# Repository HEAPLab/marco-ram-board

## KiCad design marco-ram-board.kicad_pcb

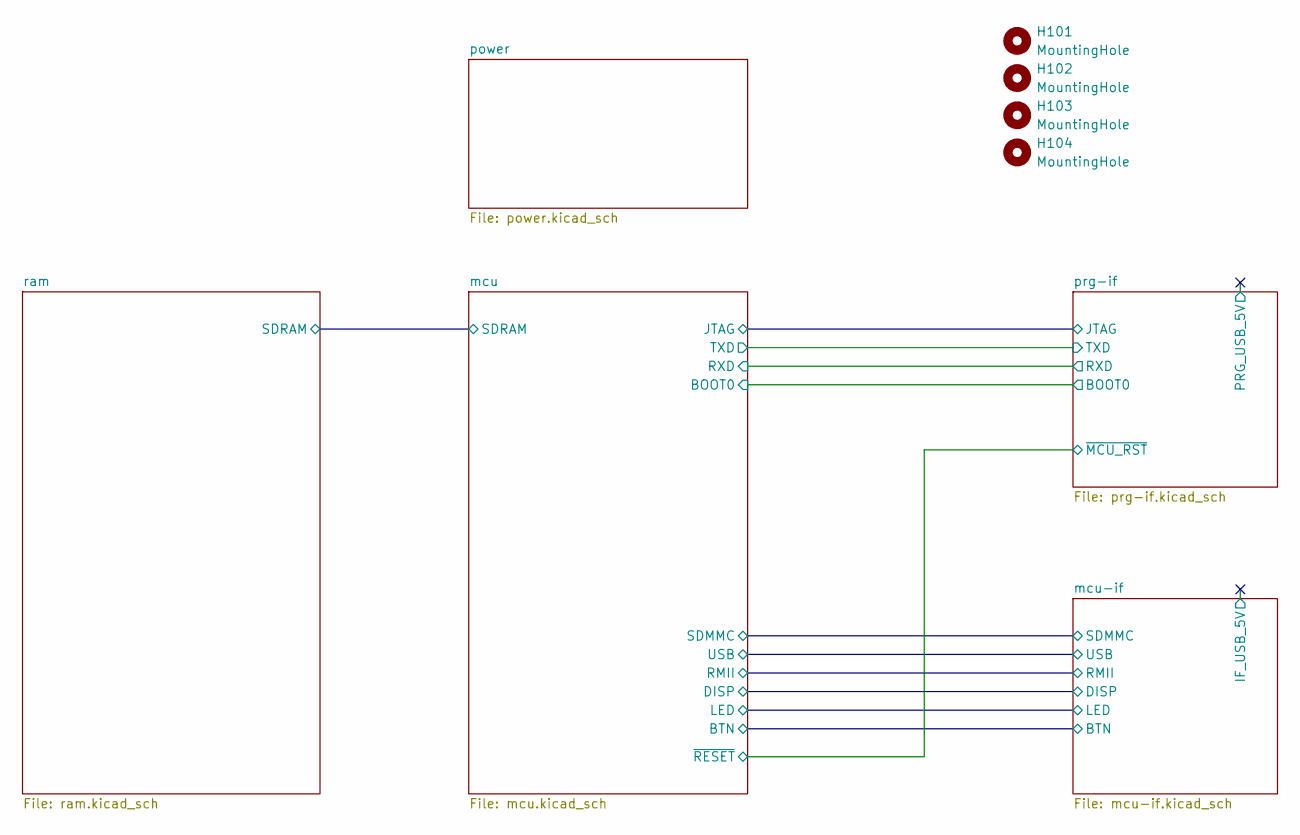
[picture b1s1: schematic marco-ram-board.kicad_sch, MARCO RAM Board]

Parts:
H101, H102, H103, H104: MountingHole; MountingHole_3.2mm_M3

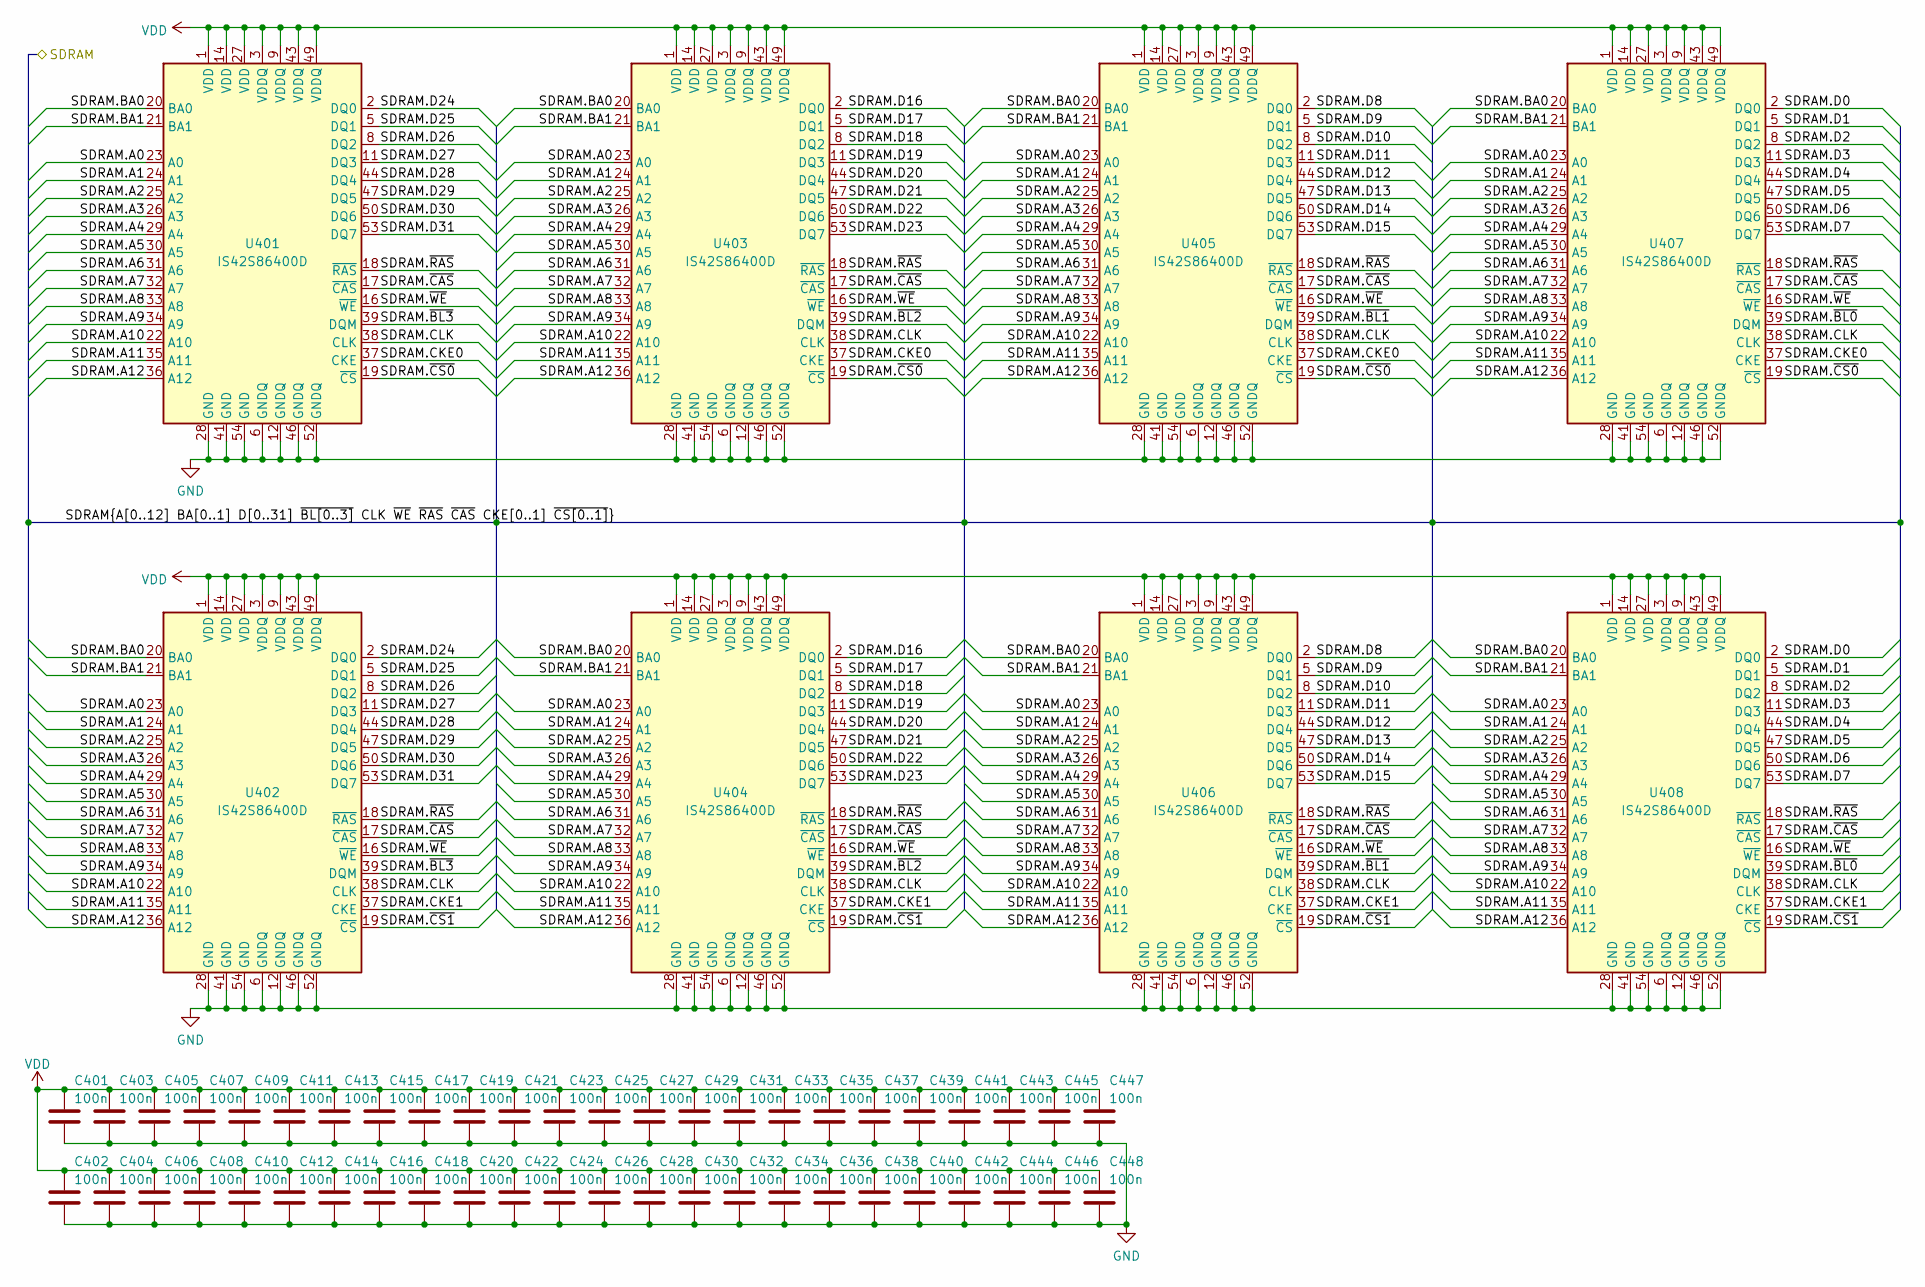
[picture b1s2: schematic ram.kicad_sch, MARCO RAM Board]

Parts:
C401, C402, C403, C404, C405, C406, C407, C408, C409, C410, C411, C412, C413, C414, C415, C416, C417, C418, C419, C420, C421, C422, C423, C424, C425, C426, C427, C428, C429, C430, C431, C432, C433, C434, C435, C436, C437, C438, C439, C440, C441, C442, C443, C444, C445, C446, C447, C448: 100n; C_0603_1608Metric_Pad1.08x0.95mm_HandSolder
U401, U402, U403, U404, U405, U406, U407, U408: IS42S86400D; TSOP-II-54_22.2x10.16mm_P0.8mm

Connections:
/mcu/SDRAM.A0: U401.23 (A0), U402.23 (A0), U403.23 (A0), U404.23 (A0), U405.23 (A0), U406.23 (A0), U407.23 (A0), U408.23 (A0); also elsewhere on the board
/mcu/SDRAM.A1: U401.24 (A1), U402.24 (A1), U403.24 (A1), U404.24 (A1), U405.24 (A1), U406.24 (A1), U407.24 (A1), U408.24 (A1); also elsewhere on the board
/mcu/SDRAM.A2: U401.25 (A2), U402.25 (A2), U403.25 (A2), U404.25 (A2), U405.25 (A2), U406.25 (A2), U407.25 (A2), U408.25 (A2); also elsewhere on the board
/mcu/SDRAM.A3: U401.26 (A3), U402.26 (A3), U403.26 (A3), U404.26 (A3), U405.26 (A3), U406.26 (A3), U407.26 (A3), U408.26 (A3); also elsewhere on the board
/mcu/SDRAM.A4: U401.29 (A4), U402.29 (A4), U403.29 (A4), U404.29 (A4), U405.29 (A4), U406.29 (A4), U407.29 (A4), U408.29 (A4); also elsewhere on the board
/mcu/SDRAM.A5: U401.30 (A5), U402.30 (A5), U403.30 (A5), U404.30 (A5), U405.30 (A5), U406.30 (A5), U407.30 (A5), U408.30 (A5); also elsewhere on the board
/mcu/SDRAM.A6: U401.31 (A6), U402.31 (A6), U403.31 (A6), U404.31 (A6), U405.31 (A6), U406.31 (A6), U407.31 (A6), U408.31 (A6); also elsewhere on the board
/mcu/SDRAM.A7: U401.32 (A7), U402.32 (A7), U403.32 (A7), U404.32 (A7), U405.32 (A7), U406.32 (A7), U407.32 (A7), U408.32 (A7); also elsewhere on the board
/mcu/SDRAM.A8: U401.33 (A8), U402.33 (A8), U403.33 (A8), U404.33 (A8), U405.33 (A8), U406.33 (A8), U407.33 (A8), U408.33 (A8); also elsewhere on the board
/mcu/SDRAM.A9: U401.34 (A9), U402.34 (A9), U403.34 (A9), U404.34 (A9), U405.34 (A9), U406.34 (A9), U407.34 (A9), U408.34 (A9); also elsewhere on the board
/mcu/SDRAM.A10: U401.22 (A10), U402.22 (A10), U403.22 (A10), U404.22 (A10), U405.22 (A10), U406.22 (A10), U407.22 (A10), U408.22 (A10); also elsewhere on the board
/mcu/SDRAM.A11: U401.35 (A11), U402.35 (A11), U403.35 (A11), U404.35 (A11), U405.35 (A11), U406.35 (A11), U407.35 (A11), U408.35 (A11); also elsewhere on the board
/mcu/SDRAM.A12: U401.36 (A12), U402.36 (A12), U403.36 (A12), U404.36 (A12), U405.36 (A12), U406.36 (A12), U407.36 (A12), U408.36 (A12); also elsewhere on the board
/mcu/SDRAM.BA0: U401.20 (BA0), U402.20 (BA0), U403.20 (BA0), U404.20 (BA0), U405.20 (BA0), U406.20 (BA0), U407.20 (BA0), U408.20 (BA0); also elsewhere on the board
/mcu/SDRAM.BA1: U401.21 (BA1), U402.21 (BA1), U403.21 (BA1), U404.21 (BA1), U405.21 (BA1), U406.21 (BA1), U407.21 (BA1), U408.21 (BA1); also elsewhere on the board
/mcu/SDRAM.CKE0: U401.37 (CKE), U403.37 (CKE), U405.37 (CKE), U407.37 (CKE); also elsewhere on the board
/mcu/SDRAM.CKE1: U402.37 (CKE), U404.37 (CKE), U406.37 (CKE), U408.37 (CKE); also elsewhere on the board
/mcu/SDRAM.CLK: U401.38 (CLK), U402.38 (CLK), U403.38 (CLK), U404.38 (CLK), U405.38 (CLK), U406.38 (CLK), U407.38 (CLK), U408.38 (CLK); also elsewhere on the board
/mcu/SDRAM.D0: U407.2 (DQ0), U408.2 (DQ0); also elsewhere on the board
/mcu/SDRAM.D1: U407.5 (DQ1), U408.5 (DQ1); also elsewhere on the board
/mcu/SDRAM.D2: U407.8 (DQ2), U408.8 (DQ2); also elsewhere on the board
/mcu/SDRAM.D3: U407.11 (DQ3), U408.11 (DQ3); also elsewhere on the board
/mcu/SDRAM.D4: U407.44 (DQ4), U408.44 (DQ4); also elsewhere on the board
/mcu/SDRAM.D5: U407.47 (DQ5), U408.47 (DQ5); also elsewhere on the board
/mcu/SDRAM.D6: U407.50 (DQ6), U408.50 (DQ6); also elsewhere on the board
/mcu/SDRAM.D7: U407.53 (DQ7), U408.53 (DQ7); also elsewhere on the board
/mcu/SDRAM.D8: U405.2 (DQ0), U406.2 (DQ0); also elsewhere on the board
/mcu/SDRAM.D9: U405.5 (DQ1), U406.5 (DQ1); also elsewhere on the board
/mcu/SDRAM.D10: U405.8 (DQ2), U406.8 (DQ2); also elsewhere on the board
/mcu/SDRAM.D11: U405.11 (DQ3), U406.11 (DQ3); also elsewhere on the board
/mcu/SDRAM.D12: U405.44 (DQ4), U406.44 (DQ4); also elsewhere on the board
/mcu/SDRAM.D13: U405.47 (DQ5), U406.47 (DQ5); also elsewhere on the board
/mcu/SDRAM.D14: U405.50 (DQ6), U406.50 (DQ6); also elsewhere on the board
/mcu/SDRAM.D15: U405.53 (DQ7), U406.53 (DQ7); also elsewhere on the board
/mcu/SDRAM.D16: U403.2 (DQ0), U404.2 (DQ0); also elsewhere on the board
/mcu/SDRAM.D17: U403.5 (DQ1), U404.5 (DQ1); also elsewhere on the board
/mcu/SDRAM.D18: U403.8 (DQ2), U404.8 (DQ2); also elsewhere on the board
/mcu/SDRAM.D19: U403.11 (DQ3), U404.11 (DQ3); also elsewhere on the board
/mcu/SDRAM.D20: U403.44 (DQ4), U404.44 (DQ4); also elsewhere on the board
/mcu/SDRAM.D21: U403.47 (DQ5), U404.47 (DQ5); also elsewhere on the board
/mcu/SDRAM.D22: U403.50 (DQ6), U404.50 (DQ6); also elsewhere on the board
/mcu/SDRAM.D23: U403.53 (DQ7), U404.53 (DQ7); also elsewhere on the board
/mcu/SDRAM.D24: U401.2 (DQ0), U402.2 (DQ0); also elsewhere on the board
/mcu/SDRAM.D25: U401.5 (DQ1), U402.5 (DQ1); also elsewhere on the board
/mcu/SDRAM.D26: U401.8 (DQ2), U402.8 (DQ2); also elsewhere on the board
/mcu/SDRAM.D27: U401.11 (DQ3), U402.11 (DQ3); also elsewhere on the board
/mcu/SDRAM.D28: U401.44 (DQ4), U402.44 (DQ4); also elsewhere on the board
/mcu/SDRAM.D29: U401.47 (DQ5), U402.47 (DQ5); also elsewhere on the board
/mcu/SDRAM.D30: U401.50 (DQ6), U402.50 (DQ6); also elsewhere on the board
/mcu/SDRAM.D31: U401.53 (DQ7), U402.53 (DQ7); also elsewhere on the board
/mcu/SDRAM.~BL0: U407.39 (DQM), U408.39 (DQM); also elsewhere on the board
/mcu/SDRAM.~BL1: U405.39 (DQM), U406.39 (DQM); also elsewhere on the board
/mcu/SDRAM.~BL2: U403.39 (DQM), U404.39 (DQM); also elsewhere on the board
/mcu/SDRAM.~BL3: U401.39 (DQM), U402.39 (DQM); also elsewhere on the board
/mcu/SDRAM.~CAS: U401.17 (~CAS), U402.17 (~CAS), U403.17 (~CAS), U404.17 (~CAS), U405.17 (~CAS), U406.17 (~CAS), U407.17 (~CAS), U408.17 (~CAS); also elsewhere on the board
/mcu/SDRAM.~CS0: U401.19 (~CS), U403.19 (~CS), U405.19 (~CS), U407.19 (~CS); also elsewhere on the board
/mcu/SDRAM.~CS1: U402.19 (~CS), U404.19 (~CS), U406.19 (~CS), U408.19 (~CS); also elsewhere on the board
/mcu/SDRAM.~RAS: U401.18 (~RAS), U402.18 (~RAS), U403.18 (~RAS), U404.18 (~RAS), U405.18 (~RAS), U406.18 (~RAS), U407.18 (~RAS), U408.18 (~RAS); also elsewhere on the board
/mcu/SDRAM.~WE: U401.16 (~WE), U402.16 (~WE), U403.16 (~WE), U404.16 (~WE), U405.16 (~WE), U406.16 (~WE), U407.16 (~WE), U408.16 (~WE); also elsewhere on the board
GND: C401.2, C402.2, C403.2, C404.2, C405.2, C406.2, C407.2, C408.2, C409.2, C410.2, C411.2, C412.2, C413.2, C414.2, C415.2, C416.2, C417.2, C418.2, C419.2, C420.2, C421.2, C422.2, C423.2, C424.2, C425.2, C426.2, C427.2, C428.2, C429.2, C430.2, C431.2, C432.2, C433.2, C434.2, C435.2, C436.2, C437.2, C438.2, C439.2, C440.2, C441.2, C442.2, C443.2, C444.2, C445.2, C446.2, C447.2, C448.2, U401.6 (GNDQ), U401.12 (GNDQ), U401.28 (GND), U401.41 (GND), U401.46 (GNDQ), U401.52 (GNDQ), U401.54 (GND), U402.6 (GNDQ), U402.12 (GNDQ), U402.28 (GND), U402.41 (GND), U402.46 (GNDQ), U402.52 (GNDQ), U402.54 (GND), U403.6 (GNDQ), U403.12 (GNDQ), U403.28 (GND), U403.41 (GND), U403.46 (GNDQ), U403.52 (GNDQ), U403.54 (GND), U404.6 (GNDQ), U404.12 (GNDQ), U404.28 (GND), U404.41 (GND), U404.46 (GNDQ), U404.52 (GNDQ), U404.54 (GND), U405.6 (GNDQ), U405.12 (GNDQ), U405.28 (GND), U405.41 (GND), U405.46 (GNDQ), U405.52 (GNDQ), U405.54 (GND), U406.6 (GNDQ), U406.12 (GNDQ), U406.28 (GND), U406.41 (GND), U406.46 (GNDQ), U406.52 (GNDQ), U406.54 (GND), U407.6 (GNDQ), U407.12 (GNDQ), U407.28 (GND), U407.41 (GND), U407.46 (GNDQ), U407.52 (GNDQ), U407.54 (GND), U408.6 (GNDQ), U408.12 (GNDQ), U408.28 (GND), U408.41 (GND), U408.46 (GNDQ), U408.52 (GNDQ), U408.54 (GND); also elsewhere on the board
VDD: C401.1, C402.1, C403.1, C404.1, C405.1, C406.1, C407.1, C408.1, C409.1, C410.1, C411.1, C412.1, C413.1, C414.1, C415.1, C416.1, C417.1, C418.1, C419.1, C420.1, C421.1, C422.1, C423.1, C424.1, C425.1, C426.1, C427.1, C428.1, C429.1, C430.1, C431.1, C432.1, C433.1, C434.1, C435.1, C436.1, C437.1, C438.1, C439.1, C440.1, C441.1, C442.1, C443.1, C444.1, C445.1, C446.1, C447.1, C448.1, U401.1 (VDD), U401.3 (VDDQ), U401.9 (VDDQ), U401.14 (VDD), U401.27 (VDD), U401.43 (VDDQ), U401.49 (VDDQ), U402.1 (VDD), U402.3 (VDDQ), U402.9 (VDDQ), U402.14 (VDD), U402.27 (VDD), U402.43 (VDDQ), U402.49 (VDDQ), U403.1 (VDD), U403.3 (VDDQ), U403.9 (VDDQ), U403.14 (VDD), U403.27 (VDD), U403.43 (VDDQ), U403.49 (VDDQ), U404.1 (VDD), U404.3 (VDDQ), U404.9 (VDDQ), U404.14 (VDD), U404.27 (VDD), U404.43 (VDDQ), U404.49 (VDDQ), U405.1 (VDD), U405.3 (VDDQ), U405.9 (VDDQ), U405.14 (VDD), U405.27 (VDD), U405.43 (VDDQ), U405.49 (VDDQ), U406.1 (VDD), U406.3 (VDDQ), U406.9 (VDDQ), U406.14 (VDD), U406.27 (VDD), U406.43 (VDDQ), U406.49 (VDDQ), U407.1 (VDD), U407.3 (VDDQ), U407.9 (VDDQ), U407.14 (VDD), U407.27 (VDD), U407.43 (VDDQ), U407.49 (VDDQ), U408.1 (VDD), U408.3 (VDDQ), U408.9 (VDDQ), U408.14 (VDD), U408.27 (VDD), U408.43 (VDDQ), U408.49 (VDDQ); also elsewhere on the board

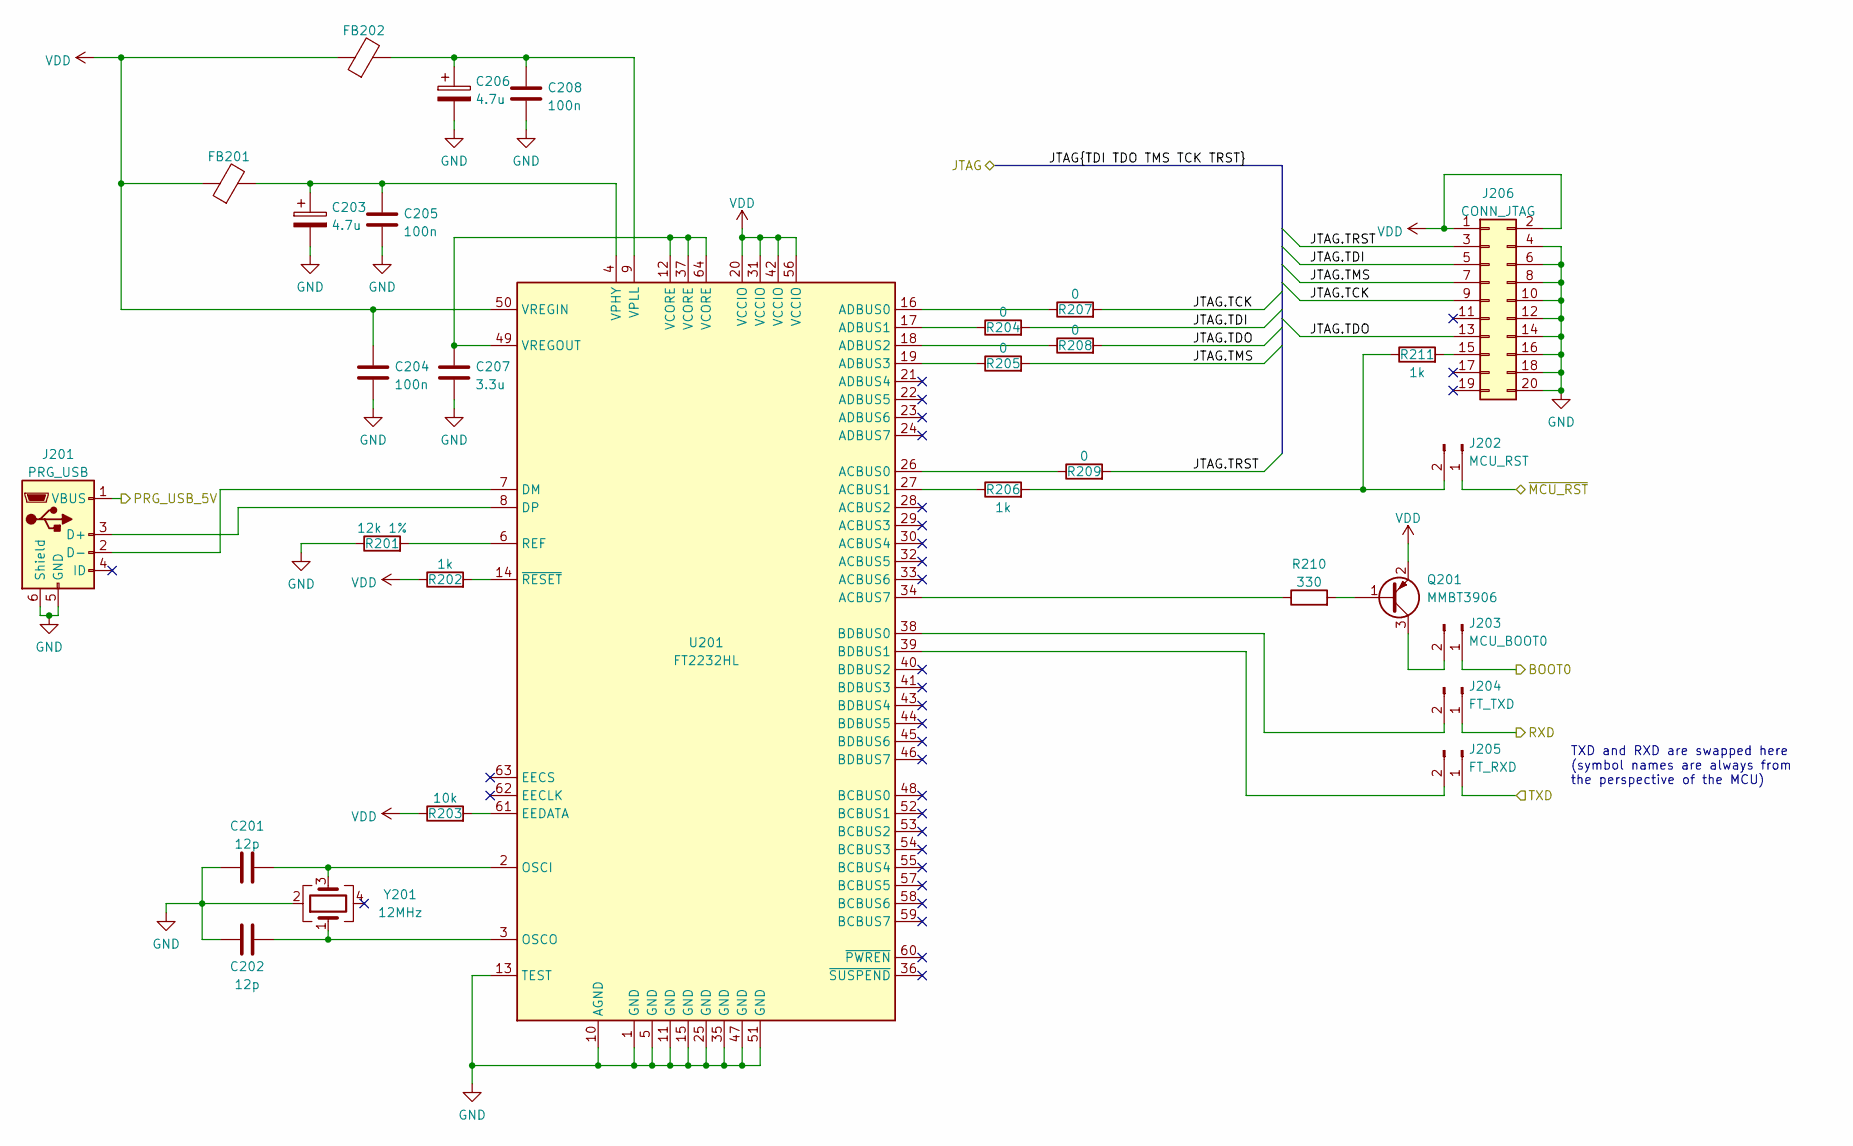
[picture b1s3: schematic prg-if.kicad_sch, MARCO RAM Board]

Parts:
C201, C202: 12p; C_0603_1608Metric_Pad1.08x0.95mm_HandSolder
C203, C206: 4.7u; CP_EIA-2012-15_AVX-P_Pad1.30x1.05mm_HandSolder; Part 647-F920J475MPA
C204, C205, C208: 100n; C_0603_1608Metric_Pad1.08x0.95mm_HandSolder
C207: 3.3u; C_0805_2012Metric_Pad1.18x1.45mm_HandSolder; Part 963-LMK212B7335KG-T
FB201, FB202: FerriteBead; L_0603_1608Metric_Pad1.05x0.95mm_HandSolder; Part 815-ACML-0603H-301
J201: PRG_USB; USB_Mini-B_Wuerth_65100516121_Horizontal
J202: MCU_RST; PinHeader_1x02_P2.54mm_Vertical
J203: MCU_BOOT0; PinHeader_1x02_P2.54mm_Vertical
J204: FT_TXD; PinHeader_1x02_P2.54mm_Vertical
J205: FT_RXD; PinHeader_1x02_P2.54mm_Vertical
J206: CONN_JTAG; PinSocket_2x10_P2.54mm_Vertical
Q201: MMBT3906; SOT-23
R201: 12k 1%; R_0603_1608Metric_Pad0.98x0.95mm_HandSolder
R202, R206, R211: 1k; R_0603_1608Metric_Pad0.98x0.95mm_HandSolder
R203: 10k; R_0603_1608Metric_Pad0.98x0.95mm_HandSolder
R204, R205, R207, R208, R209: 0; R_0603_1608Metric_Pad0.98x0.95mm_HandSolder
R210: 330; R_0603_1608Metric_Pad0.98x0.95mm_HandSolder
U201: FT2232HL; LQFP-64_10x10mm_P0.5mm
Y201: 12MHz; Crystal_SMD_5032-4Pin_5.0x3.2mm

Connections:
/mcu/BOOT0: J203.1; also elsewhere on the board
/mcu/JTAG.TCK: J206.9, R207.2; also elsewhere on the board
/mcu/JTAG.TDI: J206.5, R204.2; also elsewhere on the board
/mcu/JTAG.TDO: J206.13, R208.2; also elsewhere on the board
/mcu/JTAG.TMS: J206.7, R205.2; also elsewhere on the board
/mcu/JTAG.TRST: J206.3, R209.2; also elsewhere on the board
/mcu/RXD: J204.1; also elsewhere on the board
/mcu/TXD: J205.1; also elsewhere on the board
/mcu/~RESET: J202.1; also elsewhere on the board
/prg-if/PRG_USB_5V: J201.1 (VBUS)
GND: C201.1, C202.1, C203.2, C204.2, C205.2, C206.2, C207.2, C208.2, J201.5 (GND), J201.6 (Shield), J206.4, J206.6, J206.8, J206.10, J206.12, J206.14, J206.16, J206.18, J206.20, R201.1, U201.1 (GND), U201.5 (GND), U201.10 (AGND), U201.11 (GND), U201.13 (TEST), U201.15 (GND), U201.25 (GND), U201.35 (GND), U201.47 (GND), U201.51 (GND), Y201.2; also elsewhere on the board
unnamed: C201.2, U201.2 (OSCI), Y201.3
unnamed: C202.2, U201.3 (OSCO), Y201.1
unnamed: C203.1, C205.1, FB201.2, U201.4 (VPHY)
unnamed: C206.1, C208.1, FB202.2, U201.9 (VPLL)
unnamed: C207.1, U201.12 (VCORE), U201.37 (VCORE), U201.49 (VREGOUT), U201.64 (VCORE)
unnamed: J201.2 (D-), U201.7 (DM)
unnamed: J201.3 (D+), U201.8 (DP)
unnamed: J202.2, R206.2, R211.1
unnamed: J203.2, Q201.3 (C)
unnamed: J204.2, U201.38 (BDBUS0)
unnamed: J205.2, U201.39 (BDBUS1)
unnamed: J206.15, R211.2
unnamed: Q201.1 (B), R210.2
unnamed: R201.2, U201.6 (REF)
unnamed: R202.2, U201.14 (~RESET)
unnamed: R203.2, U201.61 (EEDATA)
unnamed: R204.1, U201.17 (ADBUS1)
unnamed: R205.1, U201.19 (ADBUS3)
unnamed: R206.1, U201.27 (ACBUS1)
unnamed: R207.1, U201.16 (ADBUS0)
unnamed: R208.1, U201.18 (ADBUS2)
unnamed: R209.1, U201.26 (ACBUS0)
unnamed: R210.1, U201.34 (ACBUS7)
VDD: C204.1, FB201.1, FB202.1, J206.1, J206.2, Q201.2 (E), R202.1, R203.1, U201.20 (VCCIO), U201.31 (VCCIO), U201.42 (VCCIO), U201.50 (VREGIN), U201.56 (VCCIO); also elsewhere on the board

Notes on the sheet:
TXD and RXD are swapped here (symbol names are always from the perspective of the MCU)

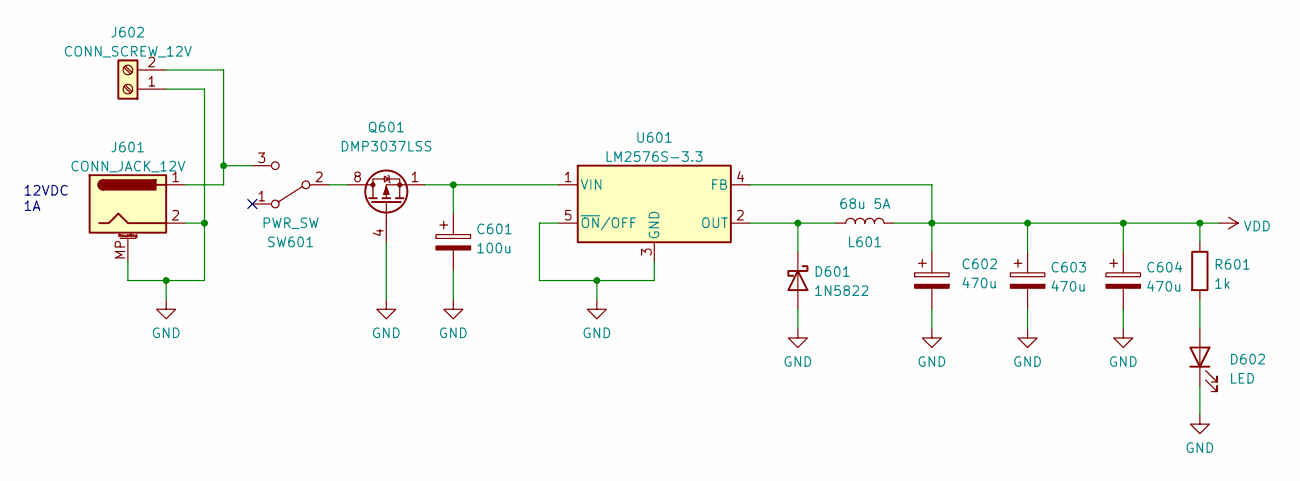
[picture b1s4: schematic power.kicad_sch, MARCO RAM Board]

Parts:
C601: 100u; CP_Radial_D6.3mm_P2.50mm; Part 710-860020473008
C602, C603, C604: 470u; CP_Radial_D8.0mm_P5.00mm; Part 667-EEU-FR1C471B
D601: 1N5822; D_DO-201AD_P5.08mm_Vertical_AnodeUp
D602: LED; LED_PLCC-2_3.4x3.0mm_KA
J601: CONN_JACK_12V; BarrelJack_CUI_PJ-063AH_Horizontal; Part 490-PJ-063AH
J602: CONN_SCREW_12V; TerminalBlock_Phoenix_MKDS-1,5-2-5.08_1x02_P5.08mm_Horizont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
L601: 68u 5A; L_Toroid_Vertical_L24.6mm_W15.5mm_P11.44mm_Pulse_KM-4; Part PE-92114KNL
Q601: DMP3037LSS; SOIC-8_3.9x4.9mm_P1.27mm
R601: 1k; R_0603_1608Metric_Pad0.98x0.95mm_HandSolder
SW601: PWR_SW; SW_Slide_CuK_1101M2xxAxx2_SPDT_RightAngle; Part 611-L101011MS02Q
U601: LM2576S-3.3; TO-263-5_TabPin3

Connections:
GND: C601.2, C602.2, C603.2, C604.2, D601.2 (A), D602.1 (K), J601.2, J601.MP (MountPin), J602.1, Q601.4 (G), U601.3 (GND), U601.5 (~ON/OFF); also elsewhere on the board
unnamed: C601.1, Q601.1 (S), Q601.2 (S), Q601.3 (S), U601.1 (VIN)
unnamed: D601.1 (K), L601.1, U601.2 (OUT)
unnamed: D602.2 (A), R601.2
unnamed: J601.1, J602.2, SW601.3 (C)
unnamed: Q601.5 (D), Q601.6 (D), Q601.7 (D), Q601.8 (D), SW601.2 (B)
VDD: C602.1, C603.1, C604.1, L601.2, R601.1, U601.4 (FB); also elsewhere on the board

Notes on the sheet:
12VDC 1A

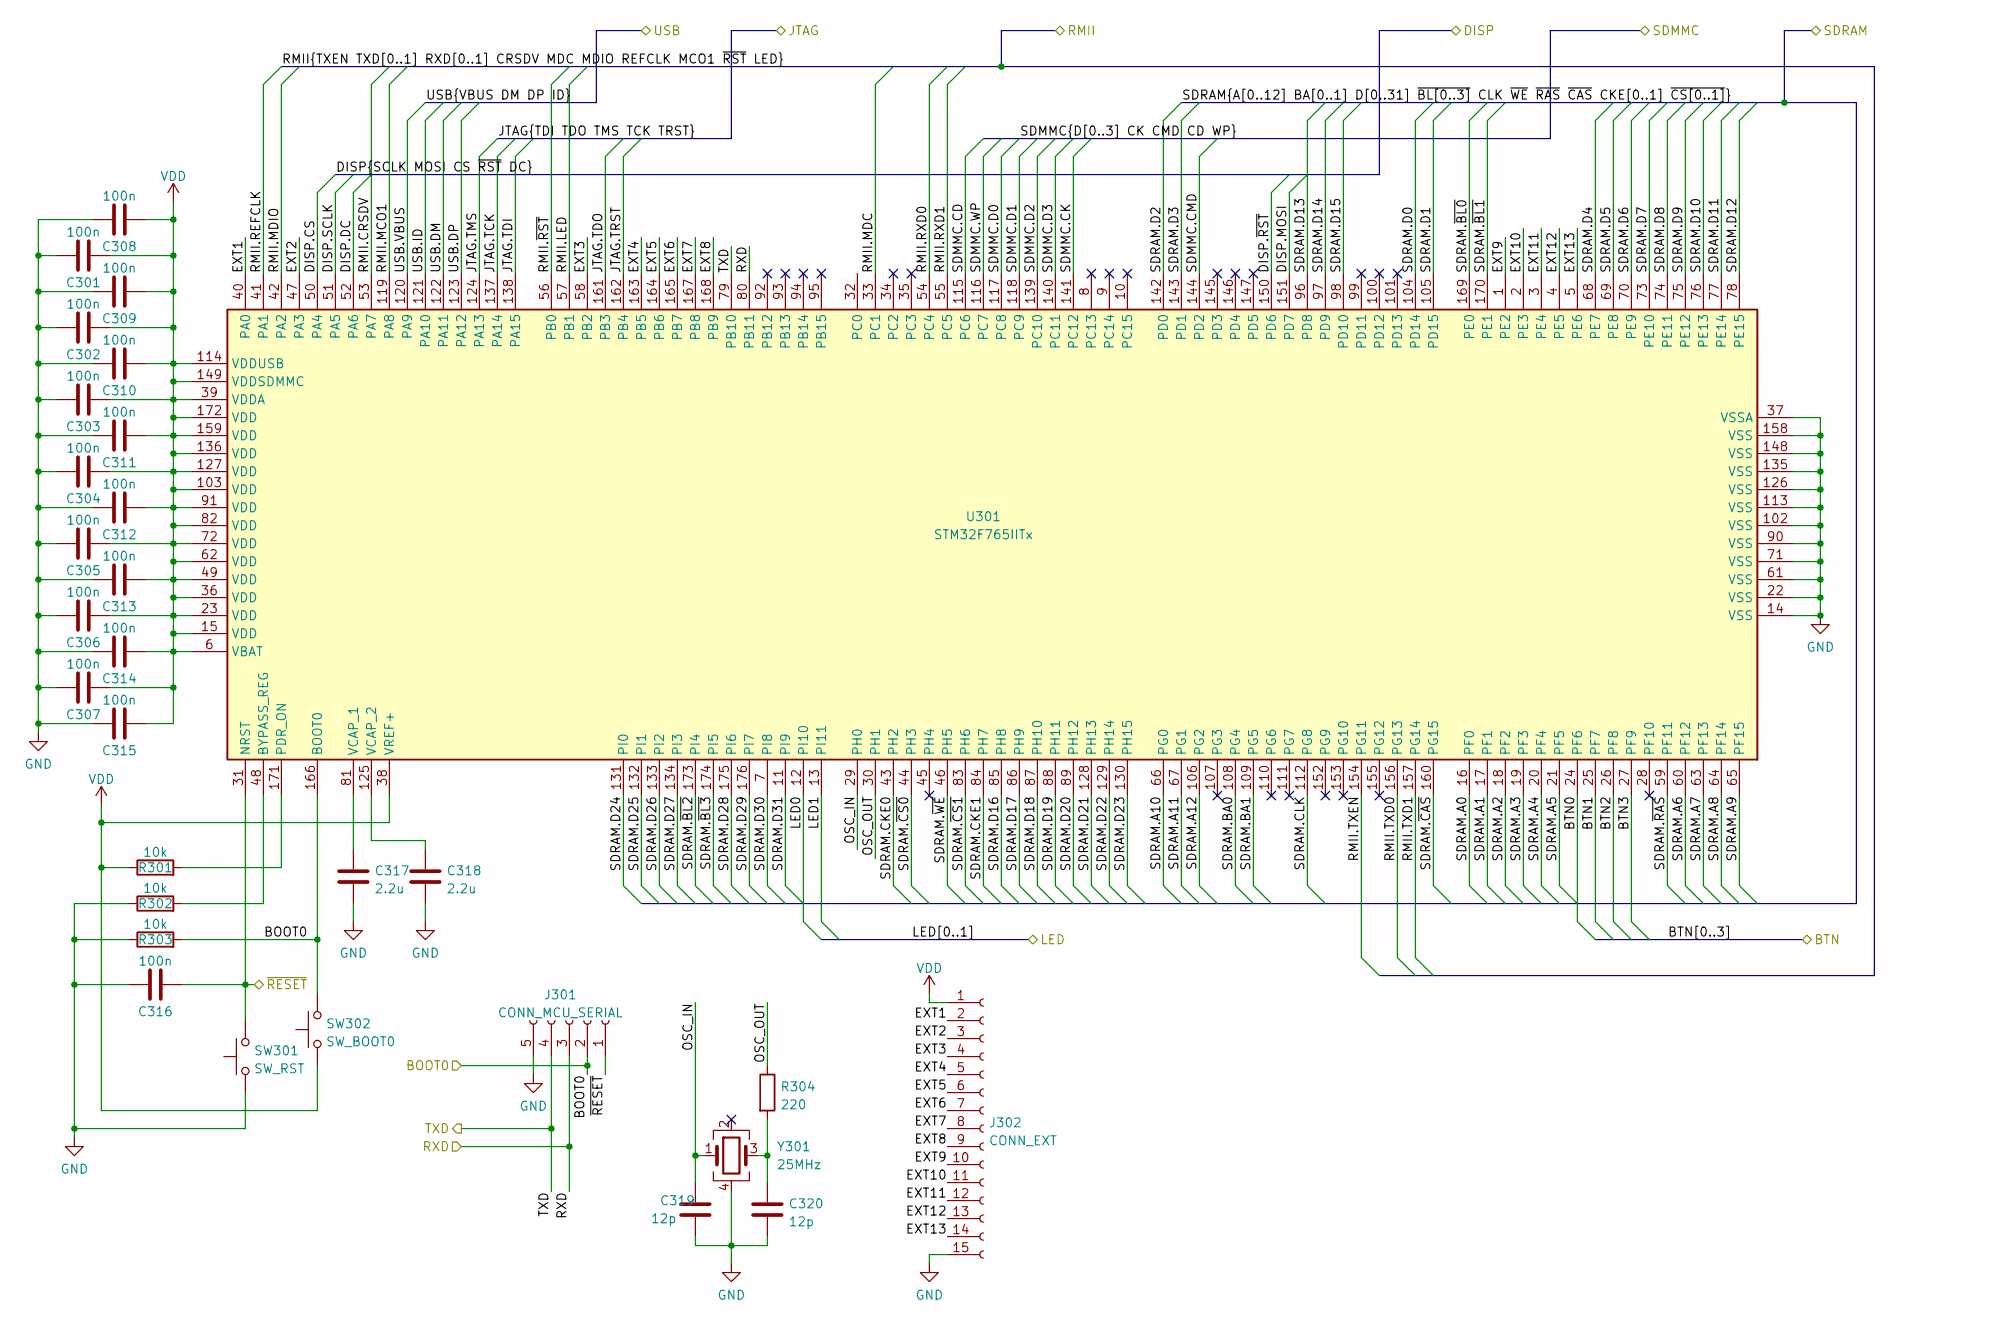
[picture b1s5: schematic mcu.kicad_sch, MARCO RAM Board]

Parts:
C301, C302, C303, C304, C305, C306, C307, C308, C309, C310, C311, C312, C313, C314, C315, C316: 100n; C_0603_1608Metric_Pad1.08x0.95mm_HandSolder
C317, C318: 2.2u; C_0805_2012Metric_Pad1.18x1.45mm_HandSolder
C319, C320: 12p; C_0603_1608Metric_Pad1.08x0.95mm_HandSolder
J301: CONN_MCU_SERIAL; PinSocket_1x05_P2.54mm_Vertical
J302: CONN_EXT; PinSocket_1x15_P2.54mm_Vertical
R301, R302, R303: 10k; R_0603_1608Metric_Pad0.98x0.95mm_HandSolder
R304: 220; R_0603_1608Metric_Pad0.98x0.95mm_HandSolder
SW301: SW_RST; DTSMW69N
SW302: SW_BOOT0; DTSMW69N
U301: STM32F765IITx; LQFP-176_24x24mm_P0.5mm
Y301: 25MHz; Crystal_SMD_5032-4Pin_5.0x3.2mm

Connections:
/mcu-if/BTN0: U301.24 (PF6); also elsewhere on the board
/mcu-if/BTN1: U301.25 (PF7); also elsewhere on the board
/mcu-if/BTN2: U301.26 (PF8); also elsewhere on the board
/mcu-if/BTN3: U301.27 (PF9); also elsewhere on the board
/mcu-if/DISP.CS: U301.50 (PA4); also elsewhere on the board
/mcu-if/DISP.DC: U301.52 (PA6); also elsewhere on the board
/mcu-if/DISP.MOSI: U301.151 (PD7); also elsewhere on the board
/mcu-if/DISP.SCLK: U301.51 (PA5); also elsewhere on the board
/mcu-if/DISP.~RST: U301.150 (PD6); also elsewhere on the board
/mcu-if/LED0: U301.12 (PI10); also elsewhere on the board
/mcu-if/LED1: U301.13 (PI11); also elsewhere on the board
/mcu-if/RMII.CRSDV: U301.53 (PA7); also elsewhere on the board
/mcu-if/RMII.LED: U301.57 (PB1); also elsewhere on the board
/mcu-if/RMII.MCO1: U301.119 (PA8); also elsewhere on the board
/mcu-if/RMII.MDC: U301.33 (PC1); also elsewhere on the board
/mcu-if/RMII.MDIO: U301.42 (PA2); also elsewhere on the board
/mcu-if/RMII.REFCLK: U301.41 (PA1); also elsewhere on the board
/mcu-if/RMII.RXD0: U301.54 (PC4); also elsewhere on the board
/mcu-if/RMII.RXD1: U301.55 (PC5); also elsewhere on the board
/mcu-if/RMII.TXD0: U301.156 (PG13); also elsewhere on the board
/mcu-if/RMII.TXD1: U301.157 (PG14); also elsewhere on the board
/mcu-if/RMII.TXEN: U301.154 (PG11); also elsewhere on the board
/mcu-if/RMII.~RST: U301.56 (PB0); also elsewhere on the board
/mcu-if/SDMMC.CD: U301.115 (PC6); also elsewhere on the board
/mcu-if/SDMMC.CK: U301.141 (PC12); also elsewhere on the board
/mcu-if/SDMMC.CMD: U301.144 (PD2); also elsewhere on the board
/mcu-if/SDMMC.D0: U301.117 (PC8); also elsewhere on the board
/mcu-if/SDMMC.D1: U301.118 (PC9); also elsewhere on the board
/mcu-if/SDMMC.D2: U301.139 (PC10); also elsewhere on the board
/mcu-if/SDMMC.D3: U301.140 (PC11); also elsewhere on the board
/mcu-if/SDMMC.WP: U301.116 (PC7); also elsewhere on the board
/mcu-if/USB.DM: U301.122 (PA11); also elsewhere on the board
/mcu-if/USB.DP: U301.123 (PA12); also elsewhere on the board
/mcu-if/USB.ID: U301.121 (PA10); also elsewhere on the board
/mcu-if/USB.VBUS: U301.120 (PA9); also elsewhere on the board
/mcu/BOOT0: J301.2, R303.2, SW302.2, U301.166 (BOOT0); also elsewhere on the board
/mcu/EXT1: J302.2, U301.40 (PA0)
/mcu/EXT2: J302.3, U301.47 (PA3)
/mcu/EXT3: J302.4, U301.58 (PB2)
/mcu/EXT4: J302.5, U301.163 (PB5)
/mcu/EXT5: J302.6, U301.164 (PB6)
/mcu/EXT6: J302.7, U301.165 (PB7)
/mcu/EXT7: J302.8, U301.167 (PB8)
/mcu/EXT8: J302.9, U301.168 (PB9)
/mcu/EXT9: J302.10, U301.1 (PE2)
/mcu/EXT10: J302.11, U301.2 (PE3)
/mcu/EXT11: J302.12, U301.3 (PE4)
/mcu/EXT12: J302.13, U301.4 (PE5)
/mcu/EXT13: J302.14, U301.5 (PE6)
/mcu/JTAG.TCK: U301.137 (PA14); also elsewhere on the board
/mcu/JTAG.TDI: U301.138 (PA15); also elsewhere on the board
/mcu/JTAG.TDO: U301.161 (PB3); also elsewhere on the board
/mcu/JTAG.TMS: U301.124 (PA13); also elsewhere on the board
/mcu/JTAG.TRST: U301.162 (PB4); also elsewhere on the board
/mcu/OSC_IN: C319.1, U301.29 (PH0), Y301.1
/mcu/OSC_OUT: R304.1, U301.30 (PH1)
/mcu/RXD: J301.3, U301.80 (PB11); also elsewhere on the board
/mcu/SDRAM.A0: U301.16 (PF0); also elsewhere on the board
/mcu/SDRAM.A1: U301.17 (PF1); also elsewhere on the board
/mcu/SDRAM.A2: U301.18 (PF2); also elsewhere on the board
/mcu/SDRAM.A3: U301.19 (PF3); also elsewhere on the board
/mcu/SDRAM.A4: U301.20 (PF4); also elsewhere on the board
/mcu/SDRAM.A5: U301.21 (PF5); also elsewhere on the board
/mcu/SDRAM.A6: U301.60 (PF12); also elsewhere on the board
/mcu/SDRAM.A7: U301.63 (PF13); also elsewhere on the board
/mcu/SDRAM.A8: U301.64 (PF14); also elsewhere on the board
/mcu/SDRAM.A9: U301.65 (PF15); also elsewhere on the board
/mcu/SDRAM.A10: U301.66 (PG0); also elsewhere on the board
/mcu/SDRAM.A11: U301.67 (PG1); also elsewhere on the board
/mcu/SDRAM.A12: U301.106 (PG2); also elsewhere on the board
/mcu/SDRAM.BA0: U301.108 (PG4); also elsewhere on the board
/mcu/SDRAM.BA1: U301.109 (PG5); also elsewhere on the board
/mcu/SDRAM.CKE0: U301.43 (PH2); also elsewhere on the board
/mcu/SDRAM.CKE1: U301.84 (PH7); also elsewhere on the board
/mcu/SDRAM.CLK: U301.112 (PG8); also elsewhere on the board
/mcu/SDRAM.D0: U301.104 (PD14); also elsewhere on the board
/mcu/SDRAM.D1: U301.105 (PD15); also elsewhere on the board
/mcu/SDRAM.D2: U301.142 (PD0); also elsewhere on the board
/mcu/SDRAM.D3: U301.143 (PD1); also elsewhere on the board
/mcu/SDRAM.D4: U301.68 (PE7); also elsewhere on the board
/mcu/SDRAM.D5: U301.69 (PE8); also elsewhere on the board
/mcu/SDRAM.D6: U301.70 (PE9); also elsewhere on the board
/mcu/SDRAM.D7: U301.73 (PE10); also elsewhere on the board
/mcu/SDRAM.D8: U301.74 (PE11); also elsewhere on the board
/mcu/SDRAM.D9: U301.75 (PE12); also elsewhere on the board
/mcu/SDRAM.D10: U301.76 (PE13); also elsewhere on the board
/mcu/SDRAM.D11: U301.77 (PE14); also elsewhere on the board
/mcu/SDRAM.D12: U301.78 (PE15); also elsewhere on the board
/mcu/SDRAM.D13: U301.96 (PD8); also elsewhere on the board
/mcu/SDRAM.D14: U301.97 (PD9); also elsewhere on the board
/mcu/SDRAM.D15: U301.98 (PD10); also elsewhere on the board
/mcu/SDRAM.D16: U301.85 (PH8); also elsewhere on the board
/mcu/SDRAM.D17: U301.86 (PH9); also elsewhere on the board
/mcu/SDRAM.D18: U301.87 (PH10); also elsewhere on the board
/mcu/SDRAM.D19: U301.88 (PH11); also elsewhere on the board
/mcu/SDRAM.D20: U301.89 (PH12); also elsewhere on the board
/mcu/SDRAM.D21: U301.128 (PH13); also elsewhere on the board
/mcu/SDRAM.D22: U301.129 (PH14); also elsewhere on the board
/mcu/SDRAM.D23: U301.130 (PH15); also elsewhere on the board
/mcu/SDRAM.D24: U301.131 (PI0); also elsewhere on the board
/mcu/SDRAM.D25: U301.132 (PI1); also elsewhere on the board
/mcu/SDRAM.D26: U301.133 (PI2); also elsewhere on the board
/mcu/SDRAM.D27: U301.134 (PI3); also elsewhere on the board
/mcu/SDRAM.D28: U301.175 (PI6); also elsewhere on the board
/mcu/SDRAM.D29: U301.176 (PI7); also elsewhere on the board
/mcu/SDRAM.D30: U301.7 (PI8); also elsewhere on the board
/mcu/SDRAM.D31: U301.11 (PI9); also elsewhere on the board
/mcu/SDRAM.~BL0: U301.169 (PE0); also elsewhere on the board
/mcu/SDRAM.~BL1: U301.170 (PE1); also elsewhere on the board
/mcu/SDRAM.~BL2: U301.173 (PI4); also elsewhere on the board
/mcu/SDRAM.~BL3: U301.174 (PI5); also elsewhere on the board
/mcu/SDRAM.~CAS: U301.160 (PG15); also elsewhere on the board
/mcu/SDRAM.~CS0: U301.44 (PH3); also elsewhere on the board
/mcu/SDRAM.~CS1: U301.83 (PH6); also elsewhere on the board
/mcu/SDRAM.~RAS: U301.59 (PF11); also elsewhere on the board
/mcu/SDRAM.~WE: U301.46 (PH5); also elsewhere on the board
/mcu/TXD: J301.4, U301.79 (PB10); also elsewhere on the board
/mcu/~RESET: C316.1, J301.1, SW301.2, U301.31 (NRST); also elsewhere on the board
GND: C301.2, C302.2, C303.2, C304.2, C305.2, C306.2, C307.2, C308.2, C309.2, C310.2, C311.2, C312.2, C313.2, C314.2, C315.2, C316.2, C317.2, C318.2, C319.2, C320.2, J301.5, J302.15, R302.1, R303.1, SW301.1, U301.14 (VSS), U301.22 (VSS), U301.37 (VSSA), U301.61 (VSS), U301.71 (VSS), U301.90 (VSS), U301.102 (VSS), U301.113 (VSS), U301.126 (VSS), U301.135 (VSS), U301.148 (VSS), U301.158 (VSS), Y301.4; also elsewhere on the board
unnamed: C317.1, U301.81 (VCAP_1)
unnamed: C318.1, U301.125 (VCAP_2)
unnamed: C320.1, R304.2, Y301.3
unnamed: R301.2, U301.171 (PDR_ON)
unnamed: R302.2, U301.48 (BYPASS_REG)
VDD: C301.1, C302.1, C303.1, C304.1, C305.1, C306.1, C307.1, C308.1, C309.1, C310.1, C311.1, C312.1, C313.1, C314.1, C315.1, J302.1, R301.1, SW302.1, U301.6 (VBAT), U301.15 (VDD), U301.23 (VDD), U301.36 (VDD), U301.38 (VREF+), U301.39 (VDDA), U301.49 (VDD), U301.62 (VDD), U301.72 (VDD), U301.82 (VDD), U301.91 (VDD), U301.103 (VDD), U301.114 (VDDUSB), U301.127 (VDD), U301.136 (VDD), U301.149 (VDDSDMMC), U301.159 (VDD), U301.172 (VDD); also elsewhere on the board
